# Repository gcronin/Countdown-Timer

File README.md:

# Countdown Timer
 
This repository includes Eagle CAD files for a two digit countdown timer based on 4029 counters.  The clock signal is adjustable with a 555 timer providing the pulses. The countdown amount is set by holding down a button.  Another button starts the countdown.  An Arduino sketch is included which can be used to set the timer and start the countdown.

The timer output switches states when the timer reaches 00.

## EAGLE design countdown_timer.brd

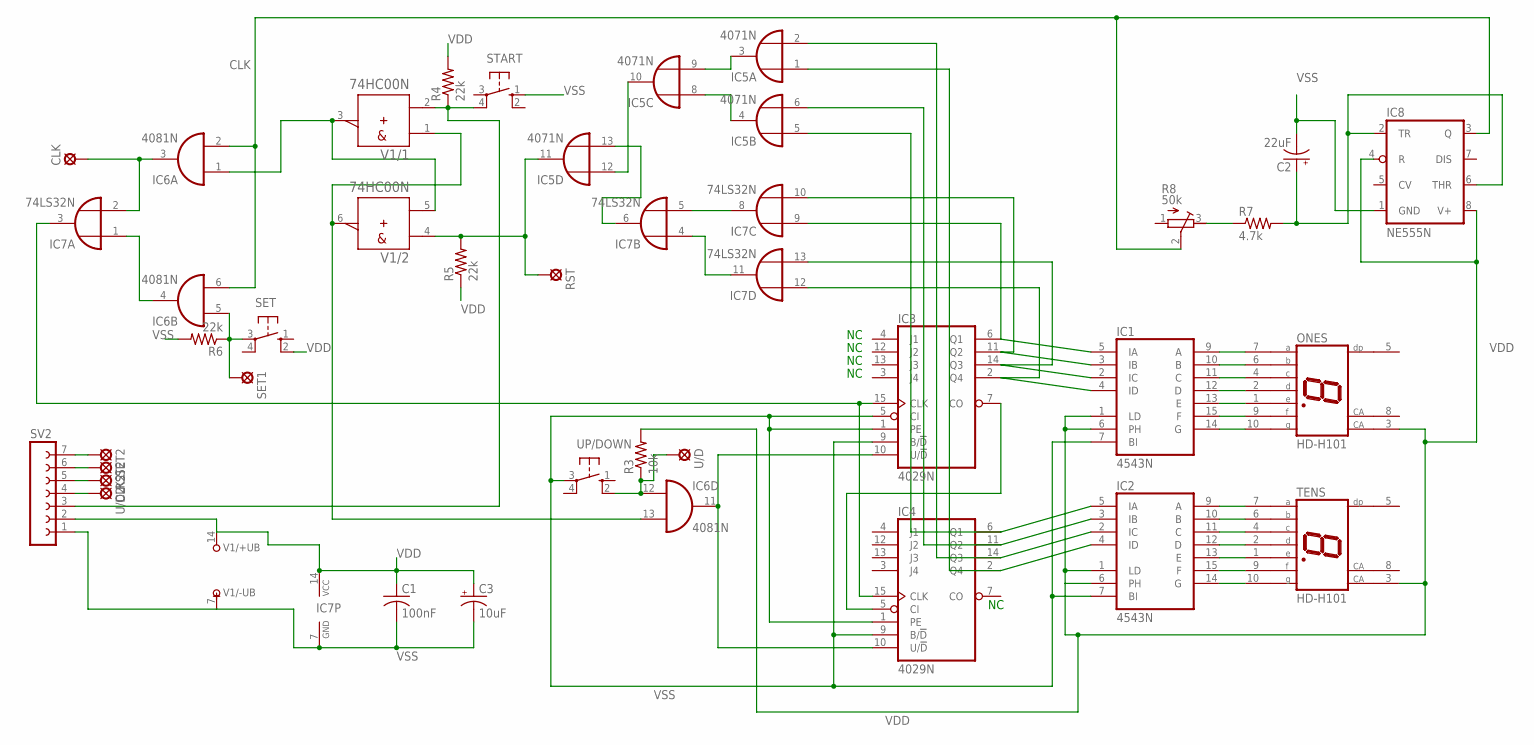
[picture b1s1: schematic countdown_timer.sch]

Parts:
C1: 100nF; C025-024X044
C2: 22uF; E3,5-8
C3: 10uF; E3,5-8
CLK, CLK2: LSP10
IC1, IC2: 4543N; DIL16
IC3, IC4: 4029N; DIL16
IC5: 4071N; DIL14
IC6: 4081N; DIL14
IC7: 74LS32N; DIL14
IC8: NE555N; DIL08
ONES: HD-H101; HDSP-M
R3: 10k; 0204/5
R4, R5, R6: 22k; 0204/5
R7: 4.7k; 0204/5
R8: 50k; RTRIM3339P
RST, RST2: LSP10
SET: 10-XX; B3F-10XX
SET1, SET2: LSP10
START: 10-XX; B3F-10XX
SV2: FE07-1; FE07
TENS: HD-H101; HDSP-M
U/D, U/D2: LSP10
UP/DOWN: 10-XX; B3F-10XX
V1: 74HC00N; DIL14

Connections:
CLK: IC6.2 (I1), IC6.6 (I1), IC8.3 (Q), R8.2 (S)
unnamed: IC2.9 (A), TENS.7 (A)
unnamed: IC2.10 (B), TENS.6 (B)
unnamed: IC2.11 (C), TENS.4 (C)
unnamed: IC2.12 (D), TENS.2 (D)
unnamed: IC2.13 (E), TENS.1 (E)
unnamed: IC2.15 (F), TENS.9 (F)
unnamed: IC2.14 (G), TENS.10 (G)
unnamed: IC1.9 (A), ONES.7 (A)
unnamed: IC1.10 (B), ONES.6 (B)
unnamed: IC1.11 (C), ONES.4 (C)
unnamed: IC1.12 (D), ONES.2 (D)
unnamed: IC1.13 (E), ONES.1 (E)
unnamed: IC1.15 (F), ONES.9 (F)
unnamed: IC1.14 (G), ONES.10 (G)
unnamed: IC7.4 (I0), IC7.11 (O)
unnamed: IC7.5 (I1), IC7.8 (O)
unnamed: IC5.4 (O), IC5.8 (I0)
unnamed: IC1.2 (IC), IC3.14 (Q3), IC7.13 (I1)
unnamed: IC2.5 (IA), IC4.6 (Q1), IC5.5 (I0)
unnamed: IC2.3 (IB), IC4.11 (Q2), IC5.6 (I1)
unnamed: IC2.2 (IC), IC4.14 (Q3), IC5.2 (I1)
unnamed: IC2.4 (ID), IC4.2 (Q4), IC5.1 (I0)
unnamed: IC3.7 (CO), IC4.5 (CI)
unnamed: IC3.10 (U/!D), IC4.10 (U/!D), IC6.11 (O)
unnamed: IC6.12 (I0), R3.1, U/D.MP, UP/DOWN.2 (S1)
unnamed: IC5.11 (O), R5.2, RST.MP, V1.4 (A)
unnamed: IC5.3 (O), IC5.9 (I1)
unnamed: IC5.10 (O), IC5.12 (I0)
unnamed: IC5.13 (I1), IC7.6 (O)
unnamed: RST2.MP, SV2.6
unnamed: CLK2.MP, SV2.5
unnamed: SV2.4, U/D2.MP
unnamed: IC6.1 (I0), V1.3 (Y), V1.5 (B)
unnamed: IC6.13 (I1), V1.1 (A), V1.6 (Y)
unnamed: R4.1, START.4 (P1), SV2.3, V1.2 (B)
unnamed: SET2.MP, SV2.7
unnamed: CLK.MP, IC6.3 (O), IC7.2 (I1)
unnamed: IC6.4 (O), IC7.1 (I0)
unnamed: IC6.5 (I0), R6.1, SET.3, SET1.MP
unnamed: IC3.15 (CLK), IC4.15 (CLK), IC7.3 (O)
unnamed: R7.1, R8.3 (E)
unnamed: C2.+, IC8.2 (TR), IC8.6 (THR), R7.2
unnamed: IC1.4 (ID), IC3.2 (Q4), IC7.12 (I0)
unnamed: IC1.3 (IB), IC3.11 (Q2), IC7.10 (I1)
unnamed: IC1.5 (IA), IC3.6 (Q1), IC7.9 (I0)
VDD: C1.1, C3.+, IC1.1 (LD), IC1.6 (PH), IC1.16 (VDD), IC2.1 (LD), IC2.6 (PH), IC2.16 (VDD), IC3.16 (VDD), IC4.16 (VDD), IC5.14 (VDD), IC6.14 (VDD), IC7.14 (VCC), IC8.4 (R), IC8.8 (V+), ONES.3 (CA), R3.2, R4.2, R5.1, SET.2 (S1), SV2.2, TENS.3 (CA), V1.14 (+UB)
VSS: C1.2, C2.-, C3.-, IC1.7 (BI), IC1.8 (VSS), IC2.7 (BI), IC2.8 (VSS), IC3.1 (PE), IC3.5 (CI), IC3.8 (VSS), IC3.9 (B/!D), IC4.1 (PE), IC4.8 (VSS), IC4.9 (B/!D), IC5.7 (VSS), IC6.7 (VSS), IC7.7 (GND), IC8.1 (GND), R6.2, START.1 (S), SV2.1, UP/DOWN.3, V1.7 (-UB)

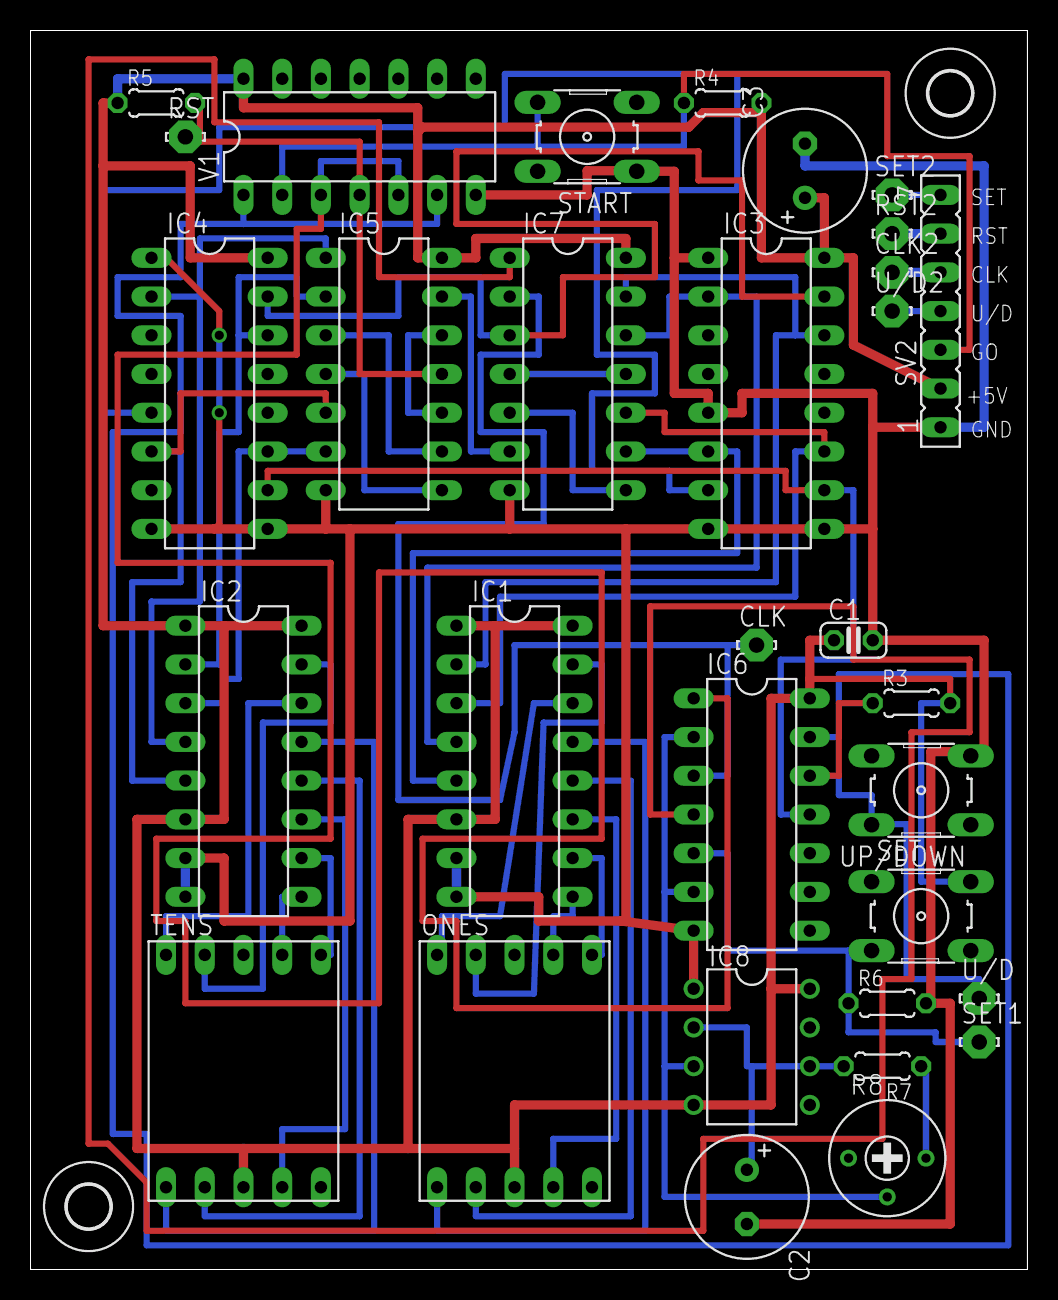
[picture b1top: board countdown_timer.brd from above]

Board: 2 copper layers, 65.4 x 81.3 mm, 34 parts (0 on the bottom side), 48 nets.

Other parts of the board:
U$2, U$3: 2,8

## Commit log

2022-04-04 Initial.
2022-04-04 Fixed R1/R2 resistors
    Eliminated pulldown resistors, routed directly to ground.
